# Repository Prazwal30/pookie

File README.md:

# Description:
This is a fun keychain I designed in which if the surroundings are bright than LED's turn on and if it gets dark than the mini motor starts vibrating and the LED's turn off
# Parts list:
Battery x1 Push Switch x2 Resistor x7 LED x4 NPN-transistor x1 Mini Motor x1 Photoresistor x1
 # Some Glimpses

# Slack id:prazwalroka

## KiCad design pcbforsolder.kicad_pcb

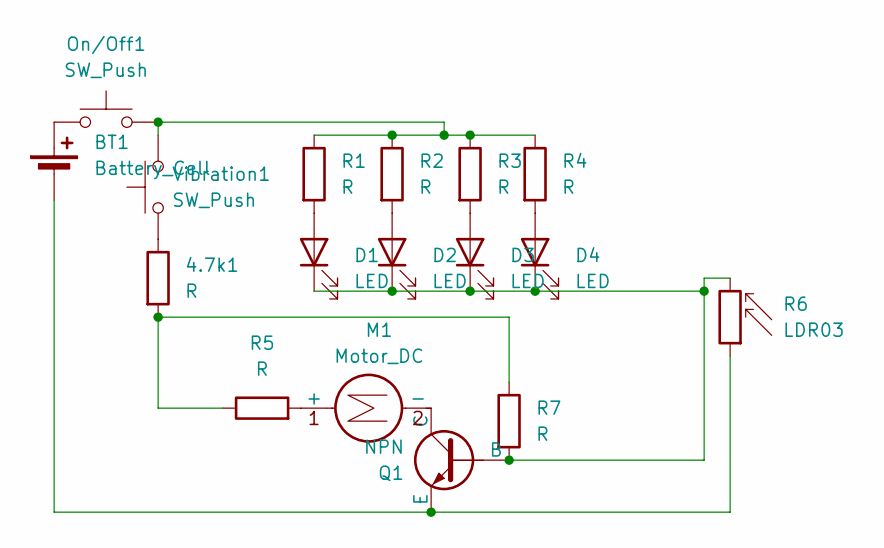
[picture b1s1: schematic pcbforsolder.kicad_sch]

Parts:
4.7k1: R; R_Axial_DIN0207_L6.3mm_D2.5mm_P7.62mm_Horizontal
BT1: Battery_Cell; BatteryHolder_Keystone_3034_1x20mm
D1, D2, D3, D4: LED; LED_D5.0mm
M1: Motor_DC; PinHeader_1x02_P2.54mm_Vertical
On/Off1: SW_Push; SW_PUSH_6mm
Q1: NPN; TO-92L_HandSolder
R1, R2, R3, R4, R5, R7: R; R_Axial_DIN0207_L6.3mm_D2.5mm_P7.62mm_Horizontal
R6: LDR03; R_LDR_5.1x4.3mm_P3.4mm_Vertical
Vibration1: SW_Push; SW_PUSH_6mm

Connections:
unnamed: 4.7k1.1, Vibration1.1
unnamed: 4.7k1.2, R5.1, R7.1
unnamed: BT1.1 (+), On/Off1.1
unnamed: BT1.2 (-), Q1.3 (E), R6.1
unnamed: D1.2 (A), R1.2
unnamed: D1.1 (K), D2.1 (K), D3.1 (K), D4.1 (K), Q1.2 (B), R6.2, R7.2
unnamed: D2.2 (A), R2.2
unnamed: D3.2 (A), R3.2
unnamed: D4.2 (A), R4.2
unnamed: M1.1 (+), R5.2
unnamed: M1.2 (-), Q1.1 (C)
unnamed: On/Off1.2, R1.1, R2.1, R3.1, R4.1, Vibration1.2

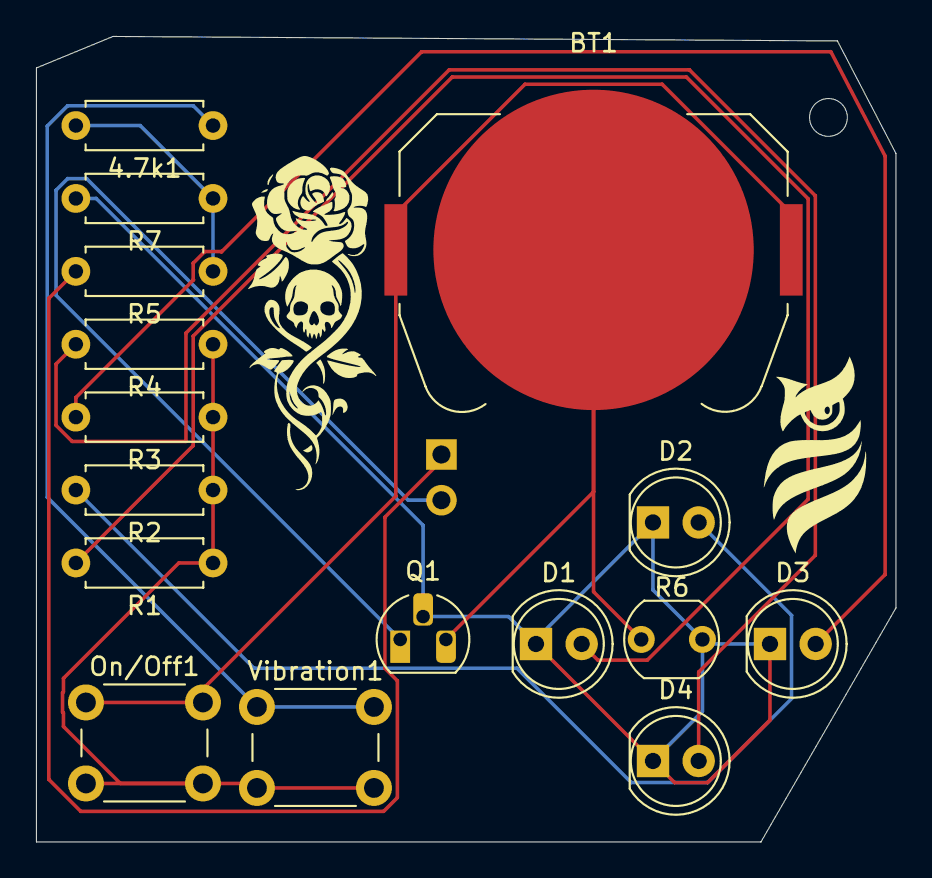
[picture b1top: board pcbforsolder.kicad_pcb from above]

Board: 2 copper layers, 47.8 x 44.8 mm, 17 parts (1 on the bottom side), 12 nets.

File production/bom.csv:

Designator,Footprint,Quantity,Value,LCSC Part #
"4.7K1, R1, R2, R3, R4, R5, R7",R_Axial_DIN0207_L6.3mm_D2.5mm_P7.62mm_Horizontal,7,R,
BT1,BatteryHolder_Keystone_3034_1x20mm,1,Battery_Cell,
"D1, D2, D3, D4",LED_D5.0mm,4,LED,
M1,PinHeader_1x02_P2.54mm_Vertical,1,Motor_DC,
"ON/OFF1, VIBRATION1",SW_PUSH_6mm,2,SW_Push,
Q1,TO-92L_HandSolder,1,NPN,
R6,R_LDR_5.1x4.3mm_P3.4mm_Vertical,1,LDR03,
